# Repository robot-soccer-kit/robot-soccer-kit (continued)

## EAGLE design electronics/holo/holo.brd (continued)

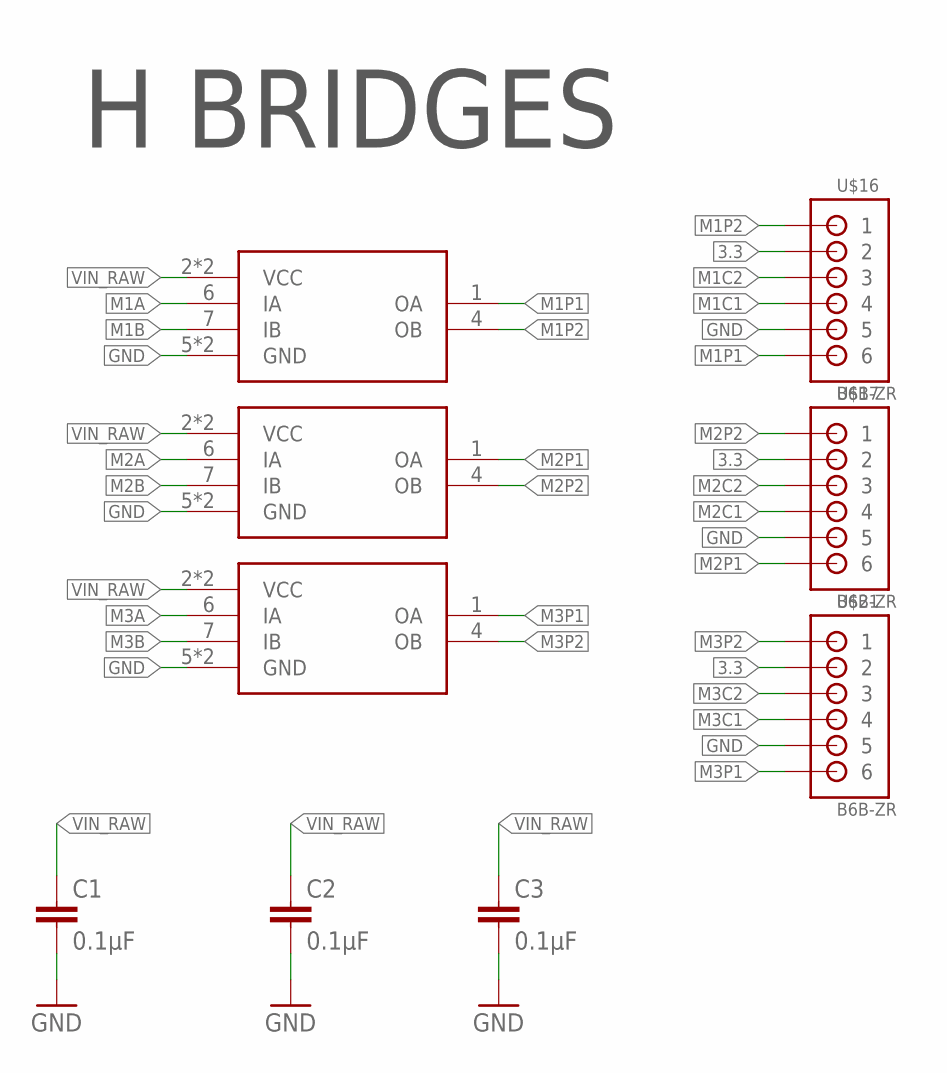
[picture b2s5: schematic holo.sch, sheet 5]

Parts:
C1, C2, C3: 0.1µF; 0805; FARNELL 2688486RL
HB1, HB2, HB3: L9110; SO8; FARNELL L9110 SOIC8
U$16, U$17, U$21: B6B-ZR; FARNELL 9491805

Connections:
3.3: U$16.2, U$17.2, U$21.2; also elsewhere on the board
GND: C1.2, C2.2, C3.2, HB1.5 (GND), HB1.8 (GND), HB2.5 (GND), HB2.8 (GND), HB3.5 (GND), HB3.8 (GND), U$16.5, U$17.5, U$21.5; also elsewhere on the board
M1A: HB1.6 (IA); also elsewhere on the board
M1B: HB1.7 (IB); also elsewhere on the board
M1C1: U$16.4; also elsewhere on the board
M1C2: U$16.3; also elsewhere on the board
M1P1: HB1.1 (OA), U$16.6
M1P2: HB1.4 (OB), U$16.1
M2A: HB2.6 (IA); also elsewhere on the board
M2B: HB2.7 (IB); also elsewhere on the board
M2C1: U$17.4; also elsewhere on the board
M2C2: U$17.3; also elsewhere on the board
M2P1: HB2.1 (OA), U$17.6
M2P2: HB2.4 (OB), U$17.1
M3A: HB3.6 (IA); also elsewhere on the board
M3B: HB3.7 (IB); also elsewhere on the board
M3C1: U$21.4; also elsewhere on the board
M3C2: U$21.3; also elsewhere on the board
M3P1: HB3.1 (OA), U$21.6
M3P2: HB3.4 (OB), U$21.1
VIN_RAW: C1.1, C2.1, C3.1, HB1.2 (VCC), HB1.3 (VCC), HB2.2 (VCC), HB2.3 (VCC), HB3.2 (VCC), HB3.3 (VCC)

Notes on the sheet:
H BRIDGES

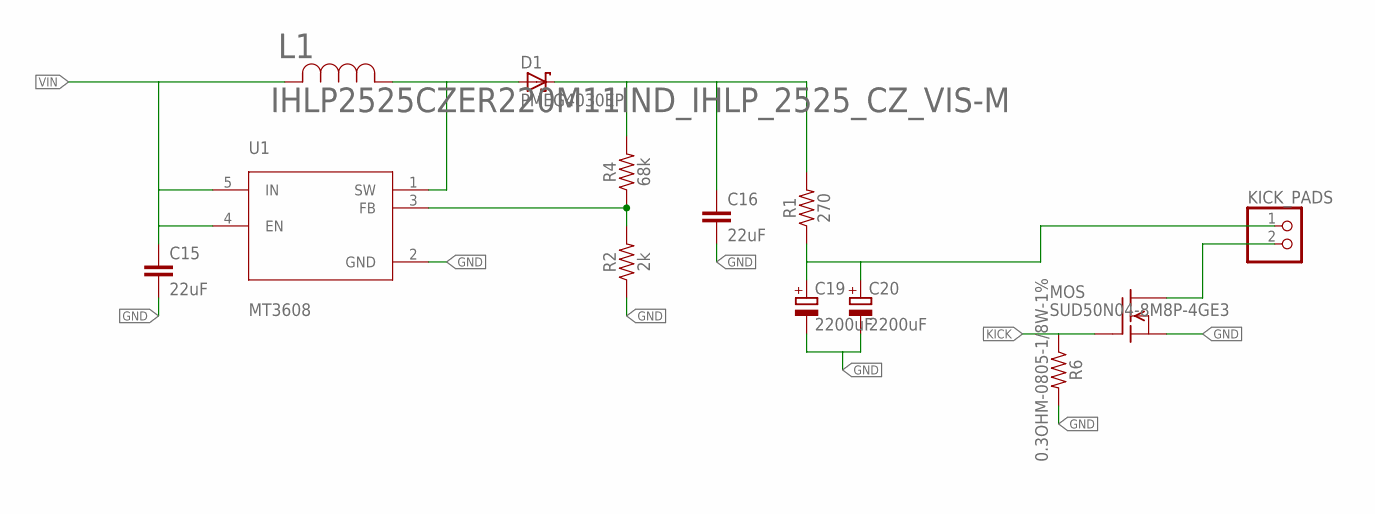
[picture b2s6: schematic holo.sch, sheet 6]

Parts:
C15, C16: 22uF; C0805; FARNELL 2666560
C19, C20: 2200uF; E5-13; FARNELL 1902893
D1: PMEG4030EP; SOD128; FARNELL 1829201
KICK_PADS: KICKER
L1: IHLP2525CZER220M11IND_IHLP_2525_CZ_VIS-M; IND_IHLP_2525_CZ_VIS-M; FARNELL 1741369
MOS: SUD50N04-8M8P-4GE3; TO252; FARNELL 1794799
R1: 270; 0805; FARNELL 1887603
R2: 2k; 0805; FARNELL MCWR08X2001FTL
R4: 68k; 0805; FARNELL 2447023
R6: 0.3OHM-0805-1/8W-1%; 0805; FARNELL 2447648
U1: MT3608; SOT95P280X145-6N; FARNELL MT3608

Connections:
GND: C15.2, C16.2, C19.-, C20.-, MOS.2 (S), R2.1, R6.2, U1.2 (GND); also elsewhere on the board
KICK: MOS.1 (G), R6.1; also elsewhere on the board
KICKER: KICK_PADS.2, MOS.3 (D)
unnamed: D1.2 (A), L1.1, U1.1 (SW)
unnamed: C16.1, D1.1 (K), R1.2, R4.2
unnamed: R2.2, R4.1, U1.3 (FB)
VIN: C15.1, L1.2, U1.4 (EN), U1.5 (IN); also elsewhere on the board
VSTORE: C19.+, C20.+, KICK_PADS.1, R1.1

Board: 2 copper layers, 73 parts (4 on the bottom side), 55 nets, no tracks yet.

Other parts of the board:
U$2, U$3, U$4, U$5, U$6, U$8, U$9, U$10, U$11, U$15, U$31, U$33, U$35, U$36, U$38, U$39: STAND-OFF

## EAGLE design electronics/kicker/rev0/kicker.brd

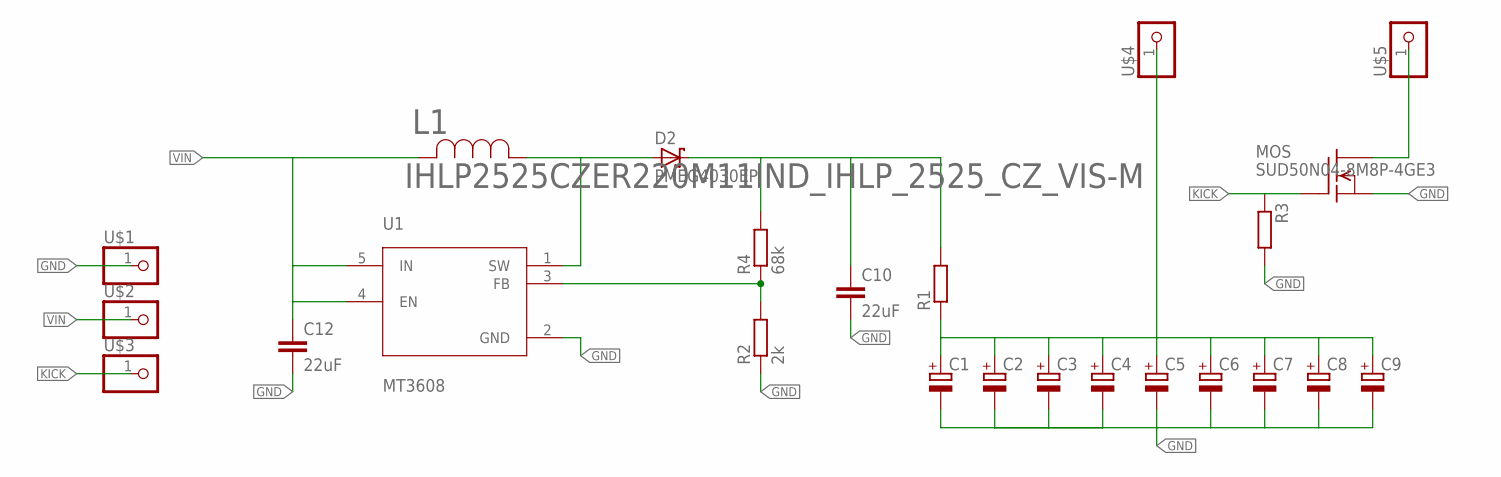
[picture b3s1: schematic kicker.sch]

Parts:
C1, C2, C3, C4, C5, C6, C7, C8, C9: CPOL-EU153CLV-1010; 153CLV-1010; FARNELL 2610827
C10, C12: 22uF; C0805; FARNELL 2611932
D2: PMEG4030EP; SOD128
L1: IHLP2525CZER220M11IND_IHLP_2525_CZ_VIS-M; IND_IHLP_2525_CZ_VIS-M; FARNELL 1741369
MOS: SUD50N04-8M8P-4GE3; TO252; FARNELL 1794799
R1: R-EU_R2010; R2010; FARNELL 1887603
R2: 2k; M0805
R3: R-EU_M0805; M0805
R4: 68k; M0805; FARNELL 2447023
U1: MT3608; SOT95P280X145-6N
U$1, U$2, U$3, U$4, U$5: CONNEC_1X01PAD; 1_PAD

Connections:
GND: C1.-, C2.-, C3.-, C4.-, C5.-, C6.-, C7.-, C8.-, C9.-, C10.2, C12.2, MOS.2 (S), R2.1, R3.2, U1.2 (GND), U$1.1
KICK: MOS.1 (G), R3.1, U$3.1
KICKER: MOS.3 (D), U$5.1
unnamed: D2.2 (A), L1.1, U1.1 (SW)
unnamed: C10.1, D2.1 (K), R1.2, R4.2
unnamed: R2.2, R4.1, U1.3 (FB)
VIN: C12.1, L1.2, U1.4 (EN), U1.5 (IN), U$2.1
VSTORE: C1.+, C2.+, C3.+, C4.+, C5.+, C6.+, C7.+, C8.+, C9.+, R1.1, U$4.1

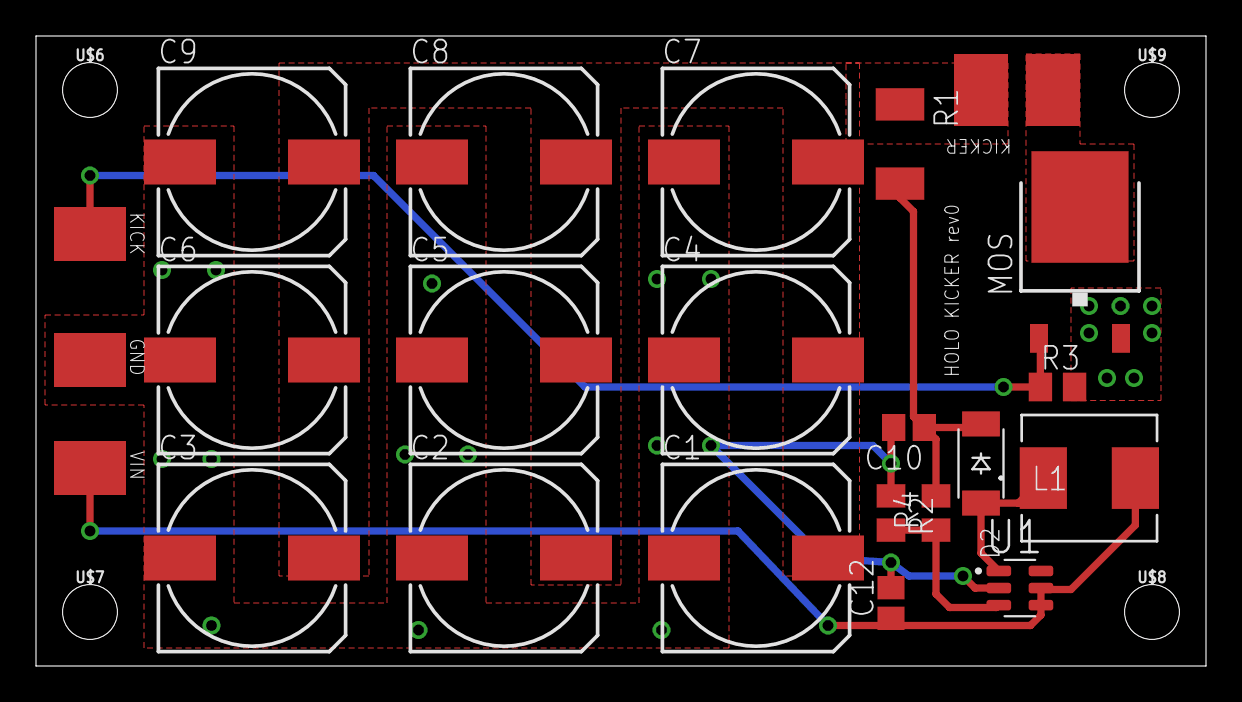
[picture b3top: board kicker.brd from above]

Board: 2 copper layers, 65.0 x 35.0 mm, 28 parts (0 on the bottom side), 8 nets.

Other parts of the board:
U$6, U$7, U$8, U$9: STAND-OFF-TIGHT

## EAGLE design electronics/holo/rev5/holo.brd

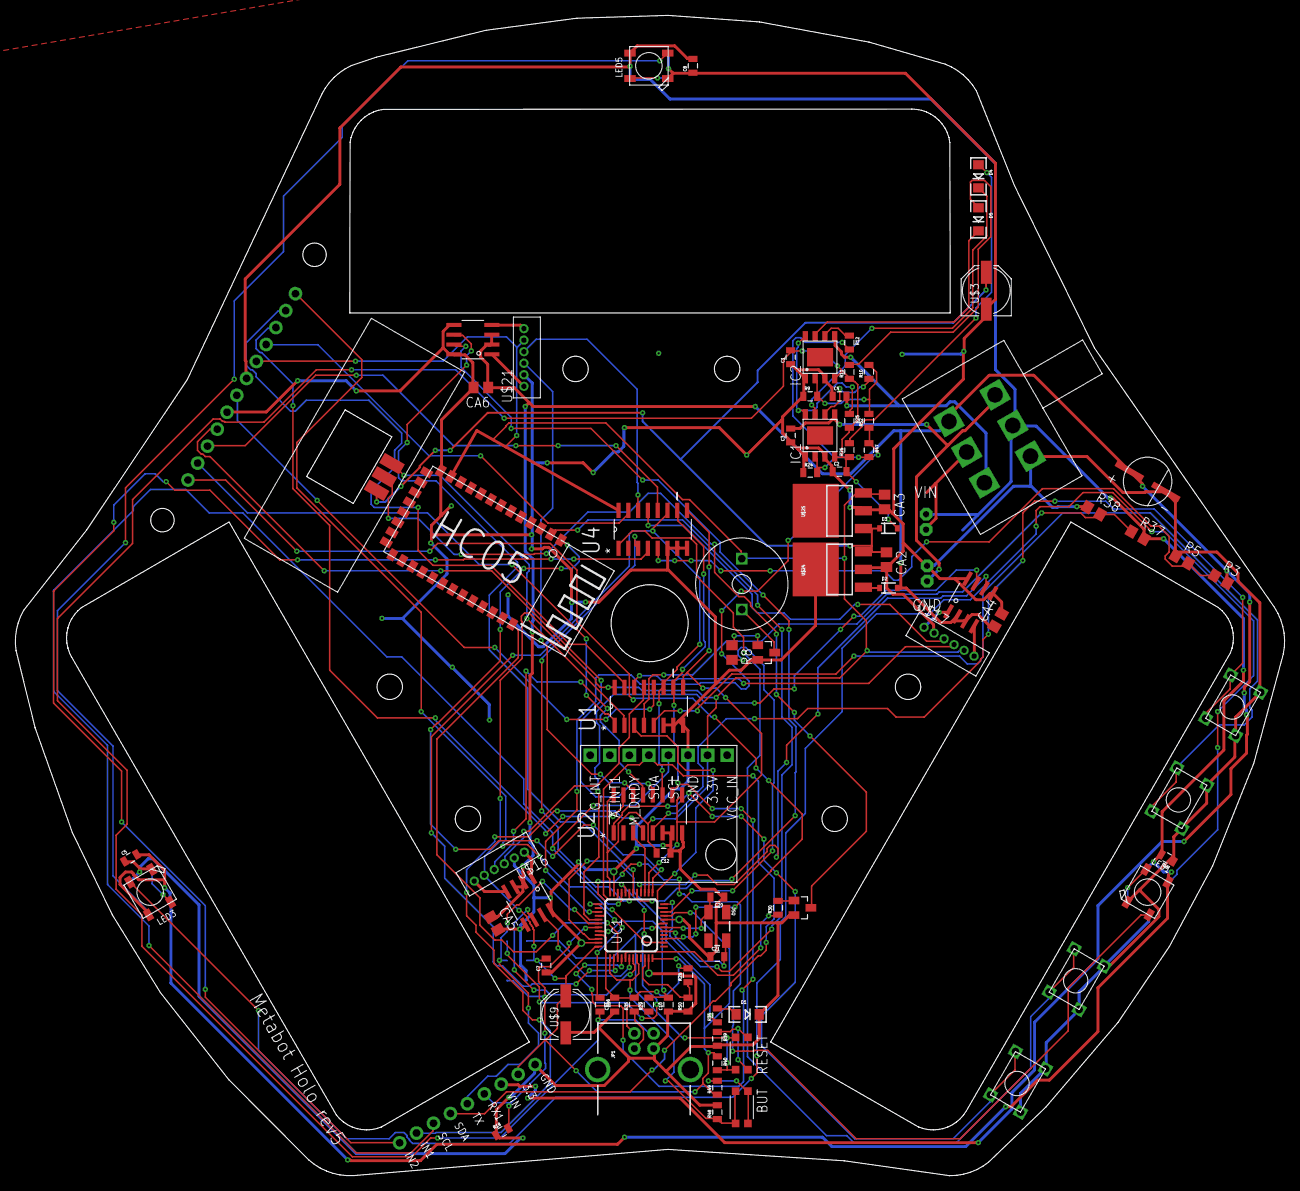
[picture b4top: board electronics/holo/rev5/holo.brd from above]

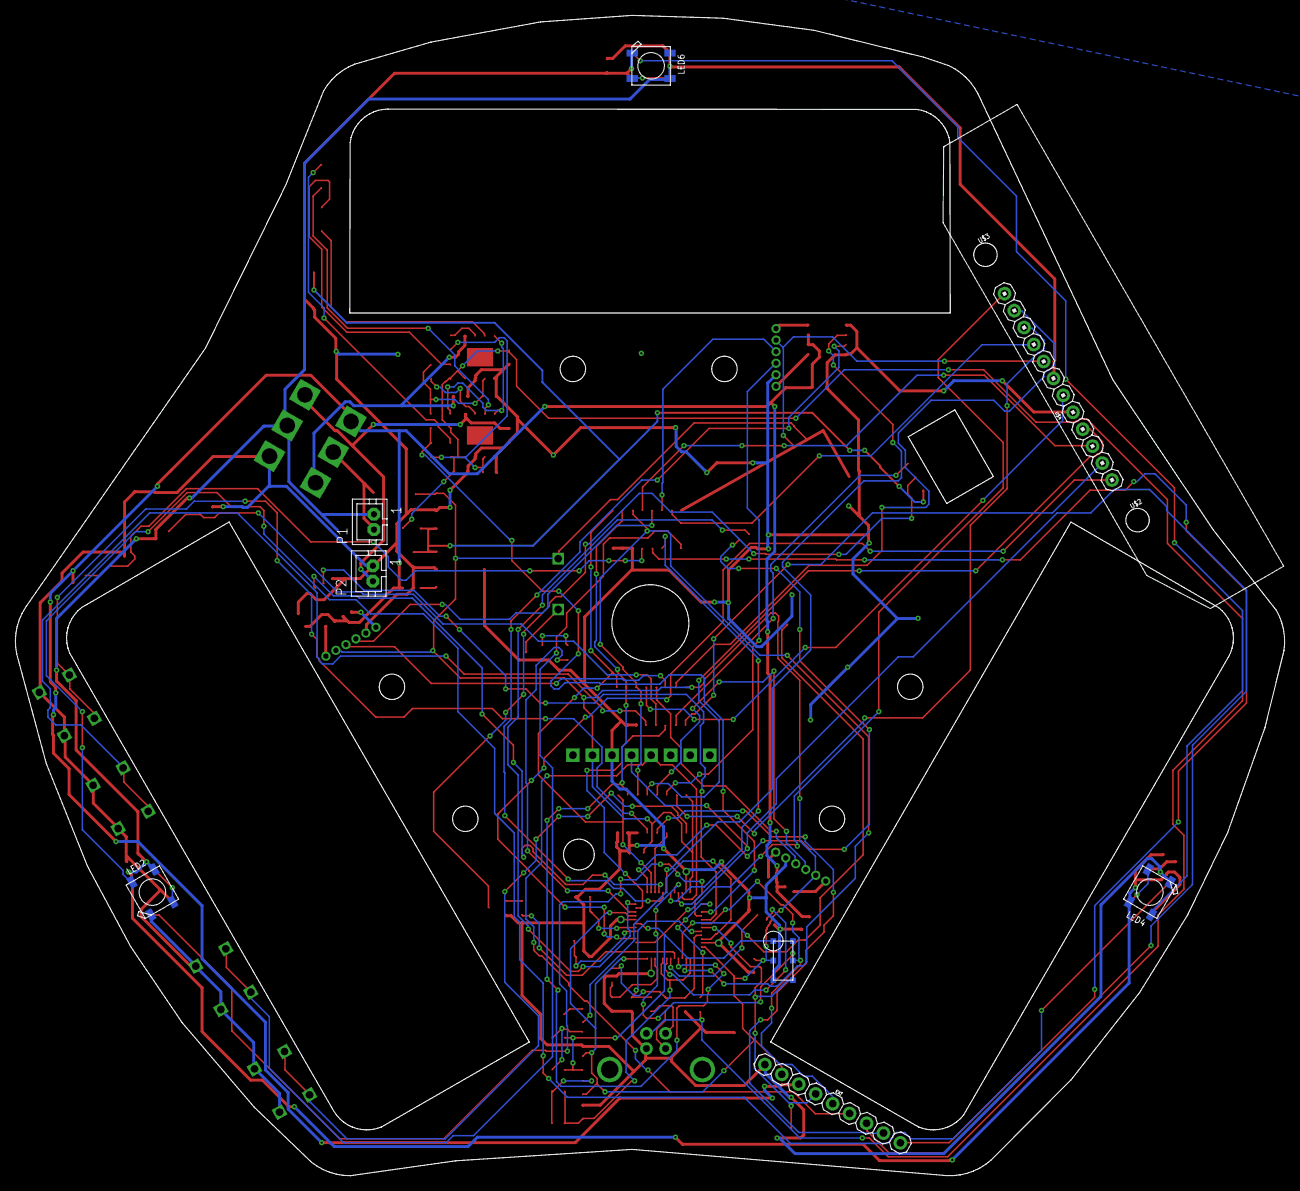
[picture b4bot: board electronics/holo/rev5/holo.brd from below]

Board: 2 copper layers, 164.8 x 150.7 mm, 98 parts (9 on the bottom side), 96 nets.

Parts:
BUT: KMR211GLFS; PUSHBUTTON-KMR241GLFS
C1, C2, C3, C4: 10uF; 0805
C5, C6, C7, C8, C12: 1uF; 0805
C10, C11: 47pF; 0805
C20, C21: 18pF; 0805
CA2, CA3, CA4, CA5, CA6: C_EU-100NF; C0805
D1, D4, D5: Blue; LED-1206
D2, D3: SOD-323
EXT: CONNEC_1X09
HB1, HB2, HB3: L9110; SO8
IC1, IC2: TP4056; SOP-8
JP1: USB-B; USB-B-PTH
LED1, LED2, LED3, LED4, LED5, LED6: WS2812B5050; WS2812B
OSC: 8MHz; CRYSTAL-SMD-5X3
P1, P2: JST-PH2
PROGRAM: CONNEC_1X066PADS; 6PADS
R3: 20K; R0805
R5, R37, R38: 10K; R0805
R8: 2K; R0805
R9, R10, R12, R24: 5K; 0805
R11, R26, R30, R36, R39, R46, R49: 1K; 0805
R18, R40, R48, R50: 10K; 0805
R25: 2K; 0805
R28: 1.5K; 0805
R29, R35: 22; 0805
R47, R52: 4K; 0805
RESET: KMR211GLFS; PUSHBUTTON-KMR241GLFS
U1, U2, U4: CD4051BM; SOIC127P600X175-16N
U$1: GY-85
U$2, U$6, U$7, U$10: 430186070716
U$3, U$9: 47uF; PANASONIC_D
U$4: HC05; HC-05
U$5: GP2; GP2_THROUGH
U$8: HOLO_OPTICALS
U$11: 220uF; PANASONIC_D8
U$12, U$18: NPN_BC817,215; SOT-23
U$13: BUZZER66
U$14: DPDT; L202021MA04Q
U$16, U$17, U$21: B6B-ZR
U$24: LM2940IMP-5.0; SOT223
U$25: TS2940CW-3.3RP; SOT223
U$31, U$33, U$35, U$36, U$38, U$39: STAND-OFF
UC1: STM32F103CBT6; LQFP48

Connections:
3.3: C7.2, C12.2, CA3.1, EXT.2, PROGRAM.2, R40.1, R49.1, U1.16, U2.16, U4.16, U$1.3.3, U$4.3.3, U$8.3.3V, U$9.+, U$13.P$2, U$16.2, U$17.2, U$21.2, U$25.3, UC1.9, UC1.24, UC1.36, UC1.48
ADDR1: U1.11, U2.11, U4.11, UC1.38
ADDR2: U1.10, U2.10, U4.10, UC1.40
ADDR3: U1.9, U2.9, U4.9, UC1.14
BAT1+: C3.2, IC1.5, P2.2, U$14.P3
BAT2+: P1.2, U$14.P5
BAT2-: C5.2, C6.2, C8.2, LED1.1-VDD, LED2.1-VDD, LED3.1-VDD, LED4.1-VDD, LED5.1-VDD, LED6.1-VDD, P1.1, R37.2, U$8.VIN, U$14.P2
BAT2CHARGE: C4.2, IC2.5, U$14.P4
BOOT1: PROGRAM.4, UC1.20
BTN1: U2.1, U$2.1, U$2.3
BTN2: U4.1, U$6.1, U$6.3
BTN3: U1.5, U$7.1, U$7.3
BTN4: U2.5, U$10.1, U$10.3
BUTTON: BUT.P$2, BUT.P$4, R48.1, UC1.37, UC1.44
BUZZER: R8.2, UC1.10
CHARGE_EN: IC1.8, IC2.8, R25.1
DISC: R28.1, R50.2, UC1.46
GND: C1.1, C2.1, C3.1, C4.1, C5.1, C6.1, C7.1, C8.1, C10.1, C11.1, C12.1, C20.1, C21.1, CA2.2, CA3.2, CA4.2, CA5.2, CA6.2, D1.C, EXT.1, HB1.5, HB1.8, HB2.5, HB2.8, HB3.5, HB3.8, IC1.1, IC1.3, IC2.1, IC2.3, JP1.GND, LED1.3-GND, LED2.3-GND, LED3.3-GND, LED4.3-GND, LED5.3-GND, LED6.3-GND, P2.1, PROGRAM.1, R5.1, R9.1, R18.1, R24.1, R38.1, R39.2, R48.2, R50.1, U1.6, U1.7, U1.8, U2.6, U2.7, U2.8, U4.6, U4.7, U4.8, U$1.GND, U$2.2, U$2.4, U$3.-, U$4.GND, U$6.2, U$6.4, U$7.2, U$7.4, U$8.GND, U$9.-, U$10.2, U$10.4, U$11.-, U$12.2, U$14.P1, U$16.5, U$17.5, U$18.2, U$21.5, U$24.2, U$24.4, U$25.2, UC1.8, UC1.23, UC1.35, UC1.47
HAS_USB: R46.1, UC1.25
IMU_SCL: EXT.7, U$1.SCL, UC1.21
IMU_SDA: EXT.6, U$1.SDA, UC1.22
IN1: EXT.8, U2.4
IN2: EXT.9, U4.4
LED: R36.1, UC1.34
LEDS: LED1.4-DIN, UC1.28
M1A: HB1.6, UC1.43
M1B: HB1.7, UC1.42
M1C1: U1.13, U$16.4
M1C2: U2.13, U$16.3
M1P1: HB1.1, U$16.6
M1P2: HB1.4, U$16.1
M2A: HB2.6, UC1.16
M2B: HB2.7, UC1.29
M2C1: U4.13, U$17.4
M2C2: U1.14, U$17.3
M2P1: HB2.1, U$17.6
M2P2: HB2.4, U$17.1
M3A: HB3.6, UC1.18
M3B: HB3.7, UC1.17
M3C1: U2.14, U$21.4
M3C2: U4.14, U$21.3
M3P1: HB3.1, U$21.6
M3P2: HB3.4, U$21.1
MORE_CHARGE: R47.1, R52.1, UC1.27
MRX: U$4.TX, UC1.13
MTX: U$4.RX, UC1.12
MUX1: U1.3, UC1.11
MUX2: U2.3, UC1.15
MUX3: U4.3, UC1.19
unnamed: D4.C, IC1.7
unnamed: R8.1, U$12.1
unnamed: U$12.3, U$13.P$1
unnamed: R39.1, RESET.P$1, RESET.P$3
unnamed: IC1.6, R10.1
unnamed: D4.A, R26.2
unnamed: D5.C, IC2.7
unnamed: IC2.6, R12.1
unnamed: D5.A, R11.2
unnamed: BUT.P$1, BUT.P$3, R49.2
unnamed: LED1.2-DOUT, LED2.4-DIN
unnamed: LED2.2-DOUT, LED3.4-DIN
unnamed: D1.A, R36.2
unnamed: LED4.2-DOUT, LED5.4-DIN
unnamed: LED5.2-DOUT, LED6.4-DIN
unnamed: R30.2, U$18.1
unnamed: LED3.2-DOUT, LED4.4-DIN
unnamed: JP1.D-, R29.1
unnamed: JP1.D+, R35.1
OPTICAL1: U1.15, U$8.O1
OPTICAL2: U2.15, U$8.O2
OPTICAL3: U4.15, U$8.O3
OPTICAL4: U1.12, U$8.O4
OPTICAL5: U2.12, U$8.O5
OPTICAL6: U4.12, U$8.O6
OPTICAL7: U1.1, U$8.O7
OPTICAL_EN1: U$8.EN1, UC1.2
OPTICAL_EN2: U$8.EN2, UC1.3
OSC_IN: C21.2, OSC.3, UC1.5
OSC_OUT: C20.2, OSC.1, UC1.6
P1: U1.2, U$5.VO
PROG1: IC1.2, R12.2, R24.2, R47.2
PROG2: IC2.2, R9.2, R10.2, R52.2
P_EN: R30.1, UC1.41
P_GND: U$5.GND, U$18.3
RESET: PROGRAM.3, R40.2, RESET.P$2, RESET.P$4, UC1.7
RX1: EXT.4, PROGRAM.6, R18.2, UC1.31
TX1: EXT.5, PROGRAM.5, UC1.30
USBDM: C10.2, R29.2, UC1.32
USBDP: C11.2, R28.2, R35.2, UC1.33
VCC: CA2.1, D3.1, U$3.+, U$5.VCC, U$24.3, U$25.1
VIN: D2.1, U$24.1
VIN_RAW: CA4.1, CA5.1, CA6.1, D2.2, EXT.3, HB1.2, HB1.3, HB2.2, HB2.3, HB3.2, HB3.3, R3.2, U$11.+, U$14.P6
VOLTAGE1: R3.1, R5.2, U4.5
VOLTAGE2: R37.1, R38.2, U1.4
VUSB: C1.2, C2.2, D3.2, IC1.4, IC2.4, JP1.VBUS, R11.1, R25.2, R26.1, R46.2
XBEECONF: U$4.KEY, UC1.39

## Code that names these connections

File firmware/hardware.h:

#ifndef _HARDWARE_H
#define _HARDWARE_H

/**
* Holo hardware configuration
*/

// optical buttons enable
#define OPTICAL_BUTTON_ENABLE 0
#define OPTICAL_NB 7

// Wheel radius [mm]
#define MODEL_WHEEL_RADIUS    35

// Distance from robot center to wheel [mm]
#define MODEL_ROBOT_RADIUS    51.4

// Wheels gear reduction ratio
#define REDUCTION_RATIO        210

// Cycles per revolution [cycles/turn]
#define WHEELS_CPR   (7*4*REDUCTION_RATIO)

// PWM max value
#define PWM_MAX_VALUE 3000

// Front offset alpha [deg]
// Changing this will change the "front" of the robot used in the kinematics
#define FRONT_OFFSET_ALPHA  0

// Wheels orientations [deg]
#define WHEEL1_ALPHA    (FRONT_OFFSET_ALPHA + 60)
#define WHEEL2_ALPHA    (FRONT_OFFSET_ALPHA + 180)
#define WHEEL3_ALPHA    (FRONT_OFFSET_ALPHA - 60)

// Delta time of the servoing (ms)
#define SERVO_DT        10

// Delta time of the speed estimation (ms), should be a multiple of above
#define SPEED_DT        50

// Motors pins mapping
#define PIN_M1A 15  // 4 CH2
#define PIN_M1B 16  // 4 CH1
#define PIN_M2A 5   // 3 CH1
#define PIN_M2B 27  // 1 CH1
#define PIN_M3A 3   // 3 CH3
#define PIN_M3B 4   // 3 CH2

// (lower) voltage per sector to trigger the robot alarm [V]
#define VOLTAGE_LIMIT   3.5

// Voltage1 resistors [ohm]
#define VOLTAGE1_R1      20
#define VOLTAGE1_R2      10

// Voltage2 resistors [ohm]
#define VOLTAGE2_R1      10
#define VOLTAGE2_R2      10

// The board (blue) led pin
#define PIN_BOARD_LED       22

// The leds (rgb daisy chained) pin
#define LEDS_SPI            2

// Enable or disable more charge pin
#define PIN_MORE_CHARGE     29

// Buzzer pin
#define PIN_BUZZER          11

// Transistor to enable or disable features
// #define PIN_DISTANCE_EN     28
#define PIN_OPTICAL_EN1     14
#define PIN_OPTICAL_EN2     13
#define DISTANCE_SENSOR_OFFSET  4.0
#define PIN_DISTANCE_EN     17

// IMU I2C port
#define I2C_IMU             I2C2

// Bluetooth configuration pin
#define PIN_BTCONF          19
#define RC_BAUDRATE         115200

// Buttons value threshold
#define BTN_THRESHOLD       50

#endif

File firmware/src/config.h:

#pragma once

#define WIFI_SSID "RSK_Field_WiFi"
#define WIFI_PASSWORD "RSK_FIELD_PASSWORD"

#define WIFI_IP "192.168.100.101"
#define WIFI_SUBNET "255.255.255.0"
#define WIFI_GATEWAY "192.168.100.254"
#define WIFI_DNS WIFI_GATEWAY

#define WIFI_UDP_PORT 7600

// Robot's name when in Bluetooth mode
#define ROBOT_NAME "RSK"
// #define FORCE_BLUETOOTH

#define KICK_PIN 33

// Wheels gear reduction ratio
#define REDUCTION_RATIO 100

// Cycles per revolution [cycles/turn]
// The minus sign is here because encoder increments in reverted order with
// respect to pwm
#define WHEELS_CPR (7 * 4 * REDUCTION_RATIO)

// Window size for speed estimation (since we are servoing at 1Khz; this can be
// considered as the amount of milliseconds used for finite differences speed
// estimation)
#define SPEED_WINDOW 5

// Does the motors (positive) rotation gets the robot rotating positively (counter-clockwise)?
#define MOTORS_ROTATION_SIGN 1

// Board revision
#define BOARD_REV2

// Wheels orientations [deg]
// In chassis frame, the front axis is the x axis running through the kicker of
// the robot Those are orientation of the driving direction of the wheels,
// assuming they rotate in the direction that makes the robot rotate p=ositively
#ifdef BOARD_REV2
#define WHEEL1_ALPHA -90
#define WHEEL2_ALPHA 30
#define WHEEL3_ALPHA 150
#else
#define WHEEL1_ALPHA 150
#define WHEEL2_ALPHA -90
#define WHEEL3_ALPHA 30
#endif

// This define uses BRAKE mode to drive the motors
// #ifdef BOARD_REV2
// #define MOTORS_BRAKE
// #endif

// Wheel radius [m]
#define MODEL_WHEEL_RADIUS 0.035

// Distance from robot center to wheel [m]
#define MODEL_ROBOT_RADIUS 0.0595

// Maximum wheels speed [rad/s]
#define MAX_WHEEL_SPEEDS 16

// Motors wiring pins (PWM for the two directions and A/B encoders)
#ifdef BOARD_REV2
#define MOTOR1_PWM1 13
#define MOTOR1_PWM2 14
#define MOTOR1_ENC1 25
#define MOTOR1_ENC2 26

#define MOTOR2_PWM1 17
#define MOTOR2_PWM2 18
#define MOTOR2_ENC1 19
#define MOTOR2_ENC2 21

#define MOTOR3_PWM1 22
#define MOTOR3_PWM2 23
#define MOTOR3_ENC1 4
#define MOTOR3_ENC2 16
#else
#define MOTOR1_PWM1 13
#define MOTOR1_PWM2 14
#define MOTOR1_ENC1 4
#define MOTOR1_ENC2 16

#define MOTOR2_PWM1 17
#define MOTOR2_PWM2 18
#define MOTOR2_ENC1 19
#define MOTOR2_ENC2 21

#define MOTOR3_PWM1 22
#define MOTOR3_PWM2 23
#define MOTOR3_ENC1 25
#define MOTOR3_ENC2 26
#endif

// LEDs pin (6 RGB addressable WS2812 LEDs)
#define LEDS 27

// Buzzer pin
#define BUZZER 32

// Input voltage sampling pin
#define VOLTAGE 34

// Voltage divider resistors (Kohms)
#define VOLTAGE_R1 20
#define VOLTAGE_R2 10

// Maximum kick duration (microseconds)
#define KICK_MAX_DURATION 20000

// Below this voltage, the robot won't start moving, between USB voltage (see
// below) and this voltage, the robot will enter alarm mode
#define VOLTAGE_MIN 6.4

// Below this voltage, the robot is considered operated with USB
#define VOLTAGE_USB 5.0

// Set to disable WiFi power saving mode (which can cause latency issues)
// #define DISABLE_WIFI_POWER_SAVING

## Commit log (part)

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2022-05-06 1.0.5
2022-05-10 Adding 1uF decoupling for motors
2022-05-11 Electronics BOM
2022-05-11 Updating 3D parts
2022-05-11 New markers
2022-05-11 Updating distance
2022-05-11 New Bluetooth filter
2022-05-11 Addign a dumb IA for test
2022-05-11 Copying infos before iterating
2022-05-11 1.0.6
2022-05-11 Hard coding BT name
2022-05-12 Using a thread to ensure safety of detection infos while processing it in referee
2022-05-12 Capping bytes
2022-05-12 More robust identify
2022-05-12 Reducing intensity of purple
2022-05-12 1.0.7
2022-05-12 Reducing LEDs brightness
2022-05-12 Details
2022-05-12 Suspending abusive attack, penalized robots are now ejected
2022-05-12 Ensuring all robots are stopped when game resume
2022-05-12 1.0.8
2022-05-12 Fixing field.pdf
2022-05-13 Using a fix focale length
2022-05-13 1.0.9
2022-05-13 Logging penalties
2022-05-13 Using height to rescale focale instead of width
2022-05-13 1.0.10
2022-05-13 Using logger instead of print() while outputing identify infos
2022-05-13 Focal and not Focale
2022-05-13 1.1.0
2022-05-22 Cover RSK 2022
2022-05-22 Cover 2022
2022-09-01 Re-routed electronics (not tested)
2022-09-01 Slight shift
2022-09-01 Little tweaks on connector's wiring
2022-09-01 CAM rev2
2022-09-02 Electronics rework wip
2022-09-02 Detail in stack
2022-09-16 Adding 5k pulling resistor between M1A and M1B
2022-09-16 RSK rev2
2022-09-16 Re-camming, minor renamings
2022-09-16 Sheet titles
2022-09-16 Updating BOM
2022-09-16 Updating BOM and ordering informations
2022-09-17 Updating STL files
2022-09-20 1234
2022-09-20 Detailing options
2022-09-20 Updating motors.cpp
2022-09-20 Centroids
2022-11-09 Remove penalties in standard configuration
2022-11-09 Creating penalty locations (fixes #66)
2022-11-10 Add time to clear the penalty spot (fixes #66)
2022-11-14 relocate penalty spots
2022-11-14 Client exceptions management (fixes #70)
2022-11-14 Re-factor of display settings
2022-11-14 Updating format (black -l 127)
2022-11-15 Add logging to Client and add new option for exceptions managements (fixes #70)
2022-11-15 Add a warning if a team does not have control (fixes #25)
2022-11-15 Reset timer with Start Game (fixes #72)
2022-11-15 Add a more visible alert for timer end
2022-11-15 Add penalty spots to video annotations
2022-11-16 Ignoring .vscode files
2022-11-17 correct color to penalty annotations
2022-11-17 fixes #da17d174c66b4794eed6b185713fb3b4ed096bd2
2022-11-22 New fixes for UI
2022-11-27 Schematics update
2022-11-27 DXL & Steps for kicker tip
2022-11-27 Kicker tips
2022-11-29 Field RSK Darker
2022-12-05 Adding D2
2022-12-05 Updating schematics
2022-12-05 Adding D2 diode
2022-12-13 patch control warning
2022-12-21 Adjusting ADC (to investigate further)
2022-12-23 Adding forward declaration for robots
2023-01-03 RSK field
2023-01-06 Black. 1.1.1
2023-01-20 patch low quality background
2023-01-20 Add simulated ball
2023-01-25 fix robot shaking on simulated view
2023-01-28 start of the simulator without collision real mode not works
2023-01-31 Kinematics utilities
2023-02-06 changed arch of simulator
2023-02-06 add simulated kick
2023-02-06 functional low reality simulator
2023-02-08 fix the simulated kick and merge simulated Detection and Video
2023-02-09 change simulated collision
2023-02-13 Simulator work in progress
2023-02-14 Simulator is working but still in progress
2023-02-16 remove video in simulator
2023-02-16 remove video in simulator 2
2023-02-16 python version maj
2023-02-17 Bootstrap update 5.3.0
2023-03-06 Simulator refactor in progress
2023-03-06 patch simulated view
2023-03-07 move card "Adding A Port" to the top
2023-03-08 typing simulator
2023-03-08 add teleportation control and front control
2023-03-08 Change field on simulator
2023-03-09 correction 82aa22eb7c17ff47068bf0eb40c197f45be2d861
2023-03-09 patch simulator and refactor
2023-03-09 patch refactor referee
2023-03-12 refactor penalty spot
2023-03-20 Add teleport, beep and leds to clients
2023-03-20 patch collision and kick issue
2023-03-24 remove print js
2023-03-24 Using URLs (serial://, sim://) instead of ports, factorizing Robots
2023-03-24 Better handling of collisions
2023-03-27 change markers SVG
2023-03-28 Add leds to simulator
2023-03-28 start drag&drop for simulator
2023-03-29 add drag&drop to simulator
2023-03-29 refactor js referee
2023-03-29 patch and add setting for simulator
2023-04-03 add ball replacement indicator in simulator
2023-04-06 some fixes
2023-04-06 add FPS in simulator
2023-04-06 fix referee history
2023-04-06 add teleport for ball to clients
2023-04-07 2.0.0
2023-04-07 Black, adding 1ms sleep
2023-04-07 2.0.1
2023-04-07 Change FPS limit of simulator viewer to 30FPS
2023-04-07 2.0.2
2023-04-18 Clean, Docs and move to file Js part of simulator
2023-04-29 Camera view should be updated anyway in the Video tab
2023-04-29 Support for opencv 4.7+ aruco API
2023-04-29 Parenthesis
2023-04-29 Removing NOBLOCK again since the timeout should be handled by RCVTIMEO
2023-04-29 Support for OpenCV 4.7 new Aruco API
2023-04-29 2.0.3
2023-04-29 Making all first Makefile rule
2023-04-29 patch referee
2023-05-02 camera run before simulated view
2023-05-02 add display setting to simulator
2023-05-03 enable abusive attack and timed circle 3s
2023-05-03 2.0.4
2023-05-09 add fps limiter
2023-05-12 Adding a competition panel
2023-05-13 Fixing index.html
2023-05-15 begin remote referee
2023-05-15 Start timer after ball placement after half time
2023-05-15 increase distance for swap cover
2023-05-21 Detail in BOM
2023-05-22 swap team sides earlier
2023-05-22 Remote referee works
2023-05-28 teleport_ball method
2023-05-28 2.0.5
2023-05-28 Y axis color
2023-05-28 2.0.6
2023-06-26 2.1.0
2023-06-26 Competition mode can be enabled with flag -c
2023-08-31 Removing useless files
2023-10-04 2.1.2 update opencv version for windows, keywords
2023-10-04 Display an information that the backend is down fix #91
2023-10-13 Enabling remote arbiter with -r
2023-10-23 fix remote
2023-11-08 Flexible ip for remote referee
2023-11-08 add appModel for remote referee
2023-11-08 fix IU navbar
2023-11-08 2.1.3 increase timeout for backend down
2023-11-08 increase timeout for updateCameras
2023-11-10 Led and buzzer when swapping covers placement
2023-11-10 documentation Client and Constants
2023-11-10 penalty pose upgrade
2023-11-10 change starting location in the simulator
2023-11-10 2.1.4
2023-11-10 2.1.5
2023-11-10 Platform specific opencv version
2023-11-15 fixc e685a70dfd82dd9f9dc004424e670518d3822f6
2023-11-16 replace reel time by simulate time in referee
2024-04-10 Update ESP32Encoder from 0.8.0 to 0.10.2 (cause old version unvailable)
2024-04-11 Adding F-shaped batteries blocker
2024-05-21 Fixing kick() prototype in abstract class
2024-05-21 Fixing duplicate lines
2024-05-24 "No Python Backend" is now a small indicator
2024-05-24 2.1.8
2024-05-30 wifi shell
2024-05-31 Broadcasting status, listing robots in GC
2024-05-31 UDP support
2024-05-31 Adding heartbeat
2024-05-31 Listening on all UDP IPs
2024-05-31 WiFi default values
2024-05-31 2.2.0
2024-06-03 BT and Wifi mode
2024-06-03 Fixing wheel rotate detection, locking when a packet was received
2024-06-03 Moving has_packet to account for heartbeat as well
2024-06-04 Fixing extra timeout for cameras api call
2024-06-04 Fixing "No Python Backend" blinking
2024-06-04 2.2.1
2024-06-20 Packaging 2.2.2 requiring numpy<2
2024-07-01 Changing WiFi example configuration in config.h
2024-07-01 Not switching to BT if motors were enabled
2024-07-01 Updating com.cpp accordingly to motors.cpp
2024-07-01 Some more comments, making PWM positive by defaults (fixes two -1)
2024-07-09 Showing configuration when WiFi is not connected
2024-08-26 Slight improvement to trigger ratio computations
2024-08-26 2.2.3
2024-09-30 Optimizing sim rendering (switching robots to SVG, using only one canvas for robots, using off-screen rendering)
2024-09-30 Adding the wait ball position in get_state to reduce API calls
2024-09-30 v2.2.4
2024-09-30 Removing debug
2024-09-30 Fixing aspect ratios
2024-09-30 v2.2.5
2024-10-02 Fixing ratios
2024-10-02 v2.2.6
2024-10-09 Enabling low delay in robot_wifi.py
2024-10-09 v2.2.7
2024-10-10 Broadcast benchmark scripts
2024-10-10 v2.3.0
2024-10-10 Detail in broadcast recv
2024-10-14 Removing now useless wifi network & subnet args
2024-10-14 v2.3.1
2024-10-15 Nicer badge for "No Python Backend"
2024-10-16 Asking for 30fps
2024-10-21 Adding --reset flag to reset the configuration
2024-10-21 Argparse --help
2024-10-21 2.3.2
2025-01-27 Torque control using motor's characteristics
2025-01-27 Slight over-estimation of friciton torques
2025-02-04 Removing old tmp source
2025-02-20 Replacing hyphenes with underscores for normalized package name
2025-02-26 Using current location instead of hard-coded 127 for APIBackend
2025-02-26 2.3.3
2025-04-06 Scheduler mode
2025-04-06 Displaying games with no team
2025-04-06 Allowing to set active games with unknown teams
2025-04-07 2.3.4
2025-04-08 2.3.5
2025-04-10 Not showing scheduler by default
2025-04-10 2.3.6
2025-04-10 Locking game controller and ignoring other packets
2025-04-10 Implementing 30s fidelity to the game controller
2025-04-11 Astar avoidance
2025-04-11 Adjusting path finding
2025-04-11 Avoiding using velocity clipping
2025-04-11 Keeping desired norm
2025-04-11 Fixing intermediary computation
2025-04-11 2.4.0
2025-04-11 Slight renamings
2025-04-11 2.4.1
2025-04-11 Adding slight foreseeing for collisions avoidance
2025-04-14 Adjusting foresee delay
2025-04-14 Removing version constraints
2025-09-21 Checking for NaN and value ranges
2025-09-21 v2.4.3
2025-09-21 Switching to pyproject.toml
2025-09-21 Including static/ in package data
2025-09-21 v2.4.4
2025-09-26 Fixing kicker_tip_1 dimension scale
2025-10-09 Robot & BOM rev3
2025-10-09 BOM rev3
2025-10-15 Bumping flash dependency to >=2, cf https://stackoverflow.com/questions/71645272/importerror-cannot-import-name-markup-from-jinja2
2025-11-05 Adding an extra test on led size
2025-11-05 v2.4.6
2025-11-08 Using NotImplementedError instead of NotImplemented
2025-11-08 Indent
2025-11-08 v2.4.7
2025-11-08 Fixing typo
2025-11-08 Using r"" regex
2025-11-08 Ruff format, threads to daemon
2025-11-08 Running ruff check --fix
2025-11-08 Fixing sahdow error
2025-11-08 Avoiding star imports
2025-11-08 Using "is" for type compare
2025-11-08 Variable details in field.py
2025-11-08 Ignoring uv .venv
2025-11-08 Adding game_controller runner script
2025-11-08 v2.4.8
2025-11-09 Adding a dry run option
2025-11-09 Run UV action
2025-11-09 Adding gc extra in run UV wheel
2025-11-09 Not starting WiFi service when in dry mode
2025-11-09 Running with UV on all platforms
2025-11-15 Not running robot wifi service in simulation
2025-11-15 v2.4.9
2025-11-17 v2.4.10
2026-03-13 Waiting for team sides to be changed before sending robots to their sides
2026-03-13 v2.4.11
2026-03-14 Signaling change for team names
2026-03-14 v2.4.12
2026-03-14 Not updating scores visually for published games
2026-03-15 Avoiding annoying switch between views
2026-03-15 v2.5.0
2026-04-19 Publishing state after detection instead of refresh decorator
2026-04-27 Removing pragma once in cpp file
2026-04-27 Adding option to disable wifi power saving
2026-04-27 Fixing missing ifdef
2026-04-27 Command enable-able power-saving
2026-04-28 Auto power saving
2026-04-29 log every info when game is running
2026-05-03 having robots knowing their led states + fixes
2026-05-18 replay interface and recording settings done
2026-05-19 fix interface replay
2026-05-20 refacto + add penalized info for replay
2026-05-21 history fix
2026-05-22 clean up
2026-05-28 added route to transmit recorded data
2026-05-28 small clean up
2026-05-28 Rolling back pyproject.toml
2026-05-28 Rolling back client.py
2026-05-28 Detail refactoring
2026-05-28 Applying ruff format
2026-05-28 Switching to Python logger, changing logic to start/stop logs
2026-05-30 Waiting for the replay file to be written to expose it in recorded_data
2026-05-30 v2.6.1
2026-06-01 began fix for enabling recording input
2026-06-01 progress bar highlighted when game is running, fixed error of empty referee_state at the beginning and added guard to prevent infinite loop on clean up history
2026-06-01 synced rec-settings input with back, and set replay at the first frame where robots are visible when initializing replay mode
2026-06-01 clean up app.css
